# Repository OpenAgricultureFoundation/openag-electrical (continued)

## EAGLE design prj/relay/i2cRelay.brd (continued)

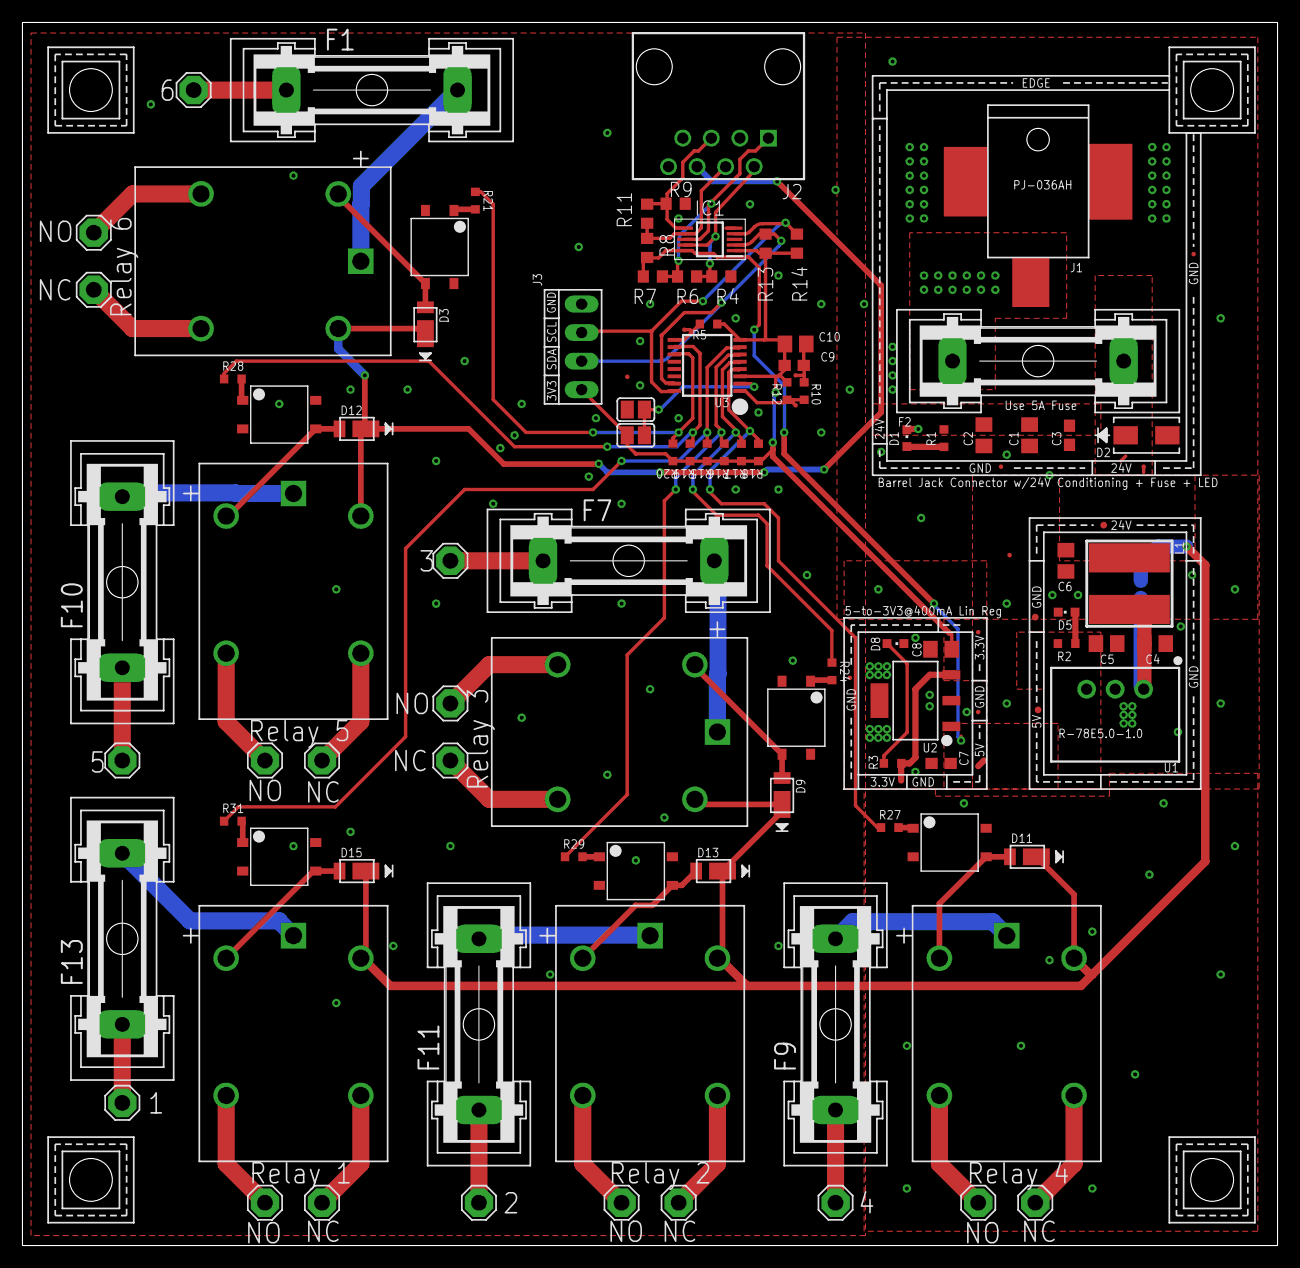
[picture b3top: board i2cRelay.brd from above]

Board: 2 copper layers, 111.7 x 108.9 mm, 120 parts (1 on the bottom side), 60 nets.

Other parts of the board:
U$1, U$2, U$4, U$5: CORNER

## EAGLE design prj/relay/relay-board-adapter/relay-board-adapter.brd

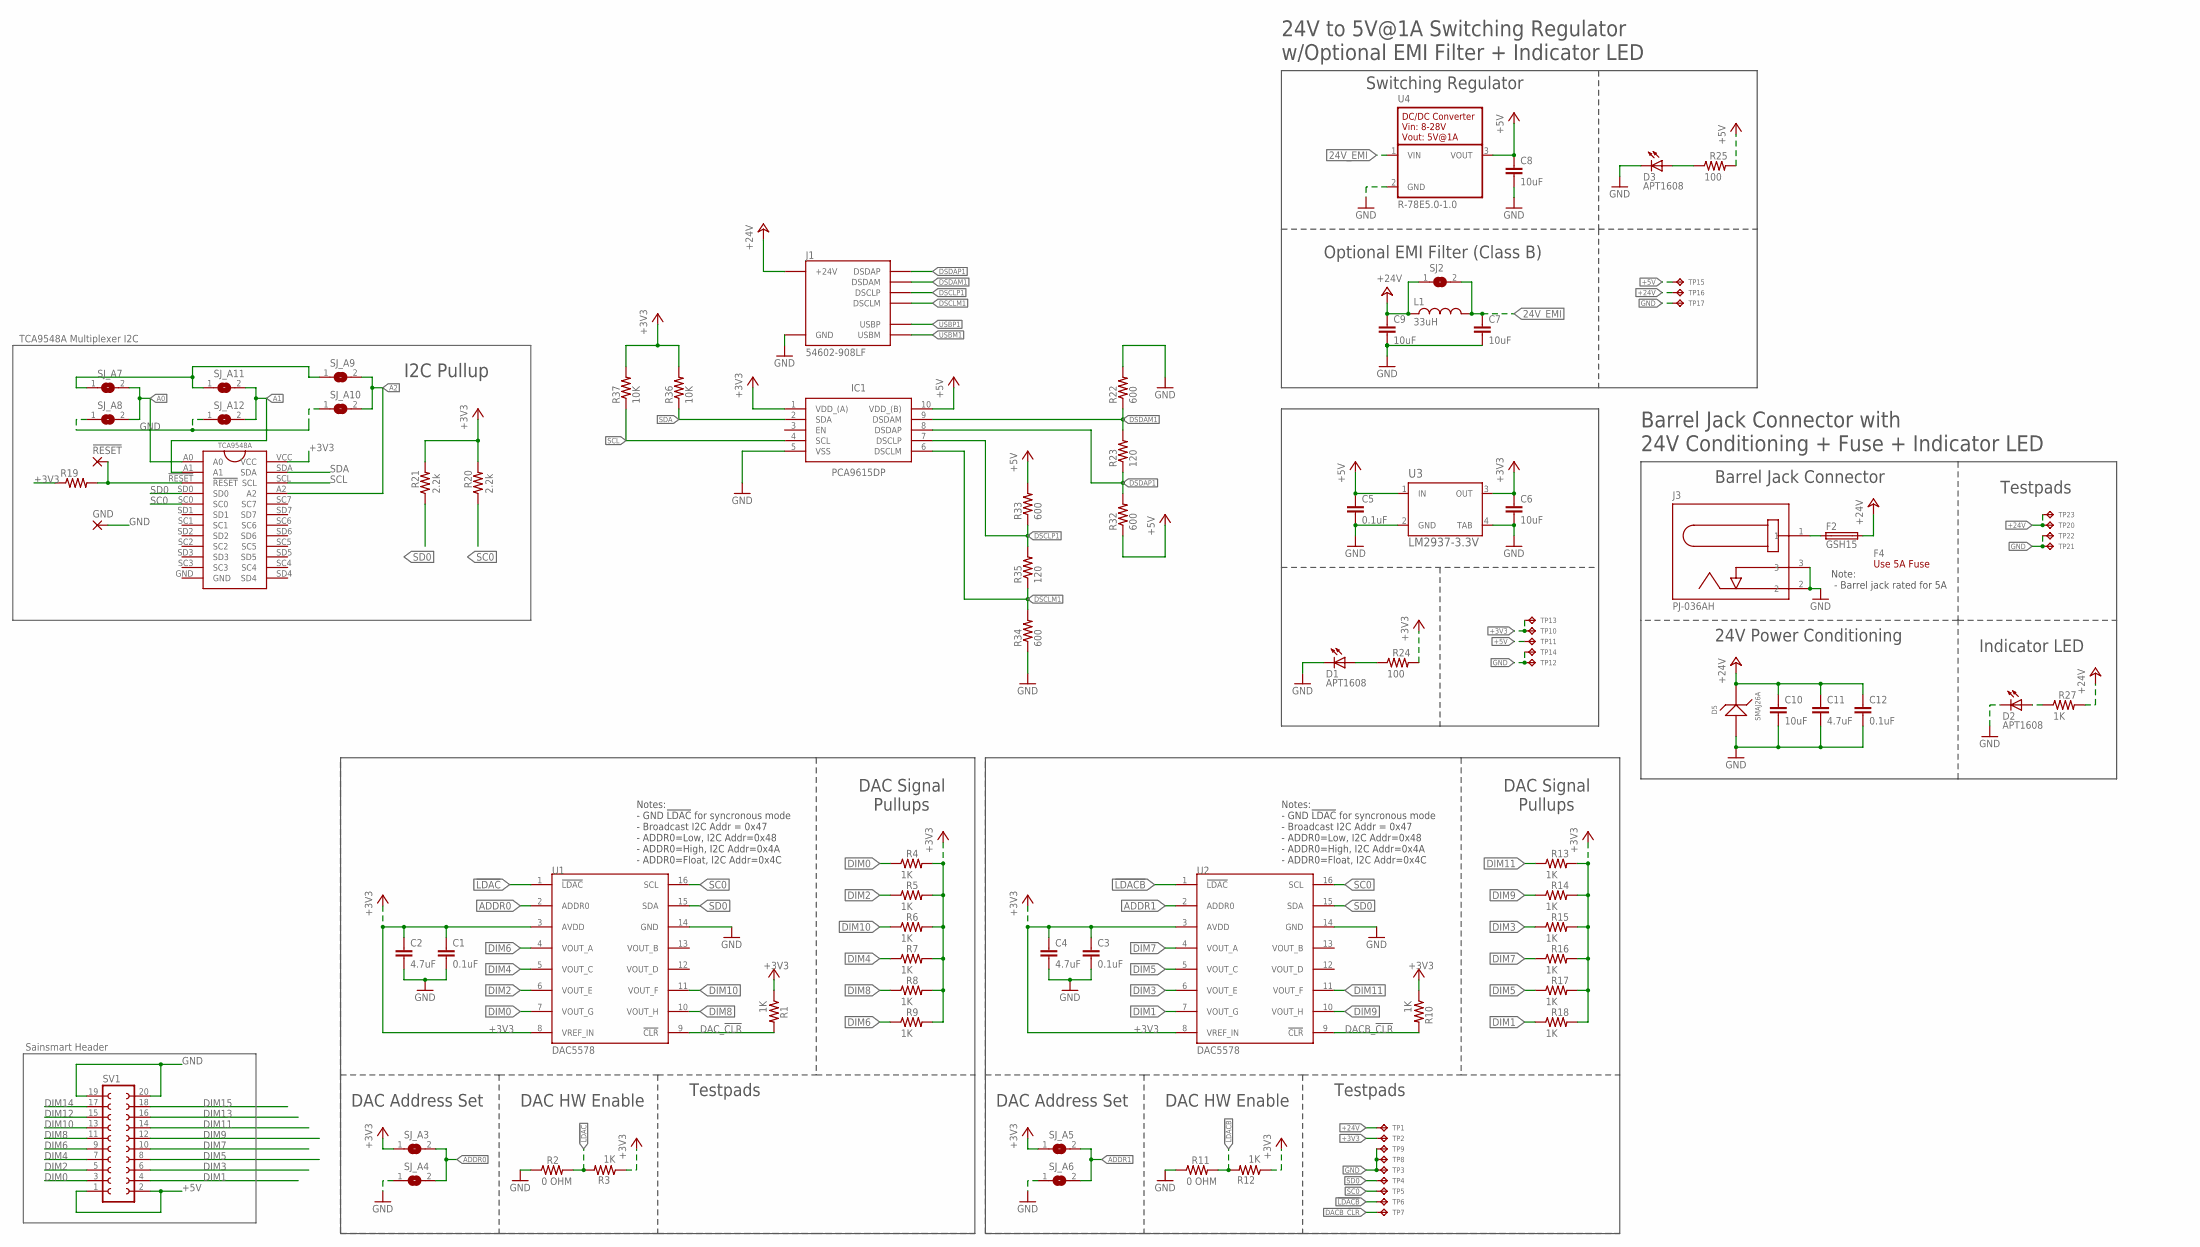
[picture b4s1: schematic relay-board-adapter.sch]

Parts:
!RESET!: 1,6/0,8
C1, C3, C5, C12: 0.1uF; C0603
C2, C4, C11: 4.7uF; C0805
C6, C7, C8, C9, C10: 10uF; C0805
D1, D2, D3: APT1608; CHIPLED_0603
D5: SMAJ26A; SMA
F2: GSH15
F4: Use 5A Fuse; FUSE-CARTRIDGE
GND: 1,6/0,8
IC1: PCA9615DP; SOP50P490X110-10N
J1: 54602-908LF; OPENAG-V1-RJ45
J3: PJ-036AH; BARREL-JACK-PJ-036AH
L1: 33uH; 29333C
R1, R3, R4, R5, R6, R7, R8, R9, R10, R12, R13, R14, R15, R16, R17, R18, R27: 1K; RC0603N
R2, R11: 0 OHM; RC0603N
R19: R-US_R0603; R0603
R20, R21: 2.2k; RC0603N
R22, R32, R33, R34: 600; R0603
R23, R35: 120; R0603
R24, R25: 100; RC0603N
R36, R37: 10K; R0603
SJ2: EMI-BYPASS
SJ_A3, SJ_A4, SJ_A5, SJ_A6, SJ_A7, SJ_A8, SJ_A9, SJ_A10, SJ_A11, SJ_A12: SOLDERJUMPERREFLOW_NOPASTE; SJ1
SV1: FE10-2
TP1, TP2, TP3, TP4, TP5, TP6, TP7, TP8, TP9, TP10, TP11, TP12, TP13, TP14, TP20, TP21, TP22, TP23: TPTP04R; TP04R
TP15, TP16, TP17: TPTP06R; TP06R
U1, U2: DAC5578; TSSOP16
U3: LM2937-3.3V; MP04A
U4: R-78E5.0-1.0
U$1: TCA9548A; TSSOP24

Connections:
24V_EMI: C7.1, L1.2, SJ2.2, U4.1 (VIN)
24V_IN1: F2.1, J3.1
!LDAC!: R2.2, R3.2, U1.1 (!LDAC!)
!LDACB!: R11.2, R12.2, TP6.1, U2.1 (!LDAC!)
!RESET!: !RESET!.1, R19.2, U$1.!RESET!
+3V3: C1.1, C2.1, C3.1, C4.1, C6.1, IC1.1 (VDD_(A)), R1.1, R3.1, R4.2, R5.2, R6.2, R7.2, R8.2, R9.2, R10.1, R12.1, R13.2, R14.2, R15.2, R16.2, R17.2, R18.2, R19.1, R20.2, R21.2, R24.2, R36.2, R37.2, SJ_A3.1, SJ_A5.1, SJ_A7.1, SJ_A9.1, SJ_A11.1, TP2.1, TP10.1, TP13.1, U1.3 (AVDD), U1.8 (VREF_IN), U2.3 (AVDD), U2.8 (VREF_IN), U3.3 (OUT), U$1.VCC
+5V: C5.1, C8.1, IC1.10 (VDD_(B)), R25.2, R32.1, R33.2, SV1.1, SV1.2, TP11.1, TP15.TP, U3.1 (IN), U4.3 (VOUT)
+24V: C9.1, C10.1, C11.1, C12.1, D5.1, F2.2, J1.24V(6) (+24V), L1.1, R27.2, SJ2.1, TP1.1, TP16.TP, TP20.1, TP23.1
A0: SJ_A7.2, SJ_A8.2, U$1.A0
A1: SJ_A11.2, SJ_A12.2, U$1.A1
A2: SJ_A9.2, SJ_A10.2, U$1.A2
ADDR0: SJ_A3.2, SJ_A4.2, U1.2 (ADDR0)
ADDR1: SJ_A5.2, SJ_A6.2, U2.2 (ADDR0)
DACB_!CLR!: R10.2, TP7.1, U2.9 (!CLR!)
DAC_!CLR!: R1.2, U1.9 (!CLR!)
DIM0: R4.1, SV1.3, U1.7 (VOUT_G)
DIM1: R18.1, SV1.4, U2.7 (VOUT_G)
DIM2: R5.1, SV1.5, U1.6 (VOUT_E)
DIM3: R15.1, SV1.6, U2.6 (VOUT_E)
DIM4: R7.1, SV1.7, U1.5 (VOUT_C)
DIM5: R17.1, SV1.8, U2.5 (VOUT_C)
DIM6: R9.1, SV1.9, U1.4 (VOUT_A)
DIM7: R16.1, SV1.10, U2.4 (VOUT_A)
DIM8: R8.1, SV1.11, U1.10 (VOUT_H)
DIM9: R14.1, SV1.12, U2.10 (VOUT_H)
DIM10: R6.1, SV1.13, U1.11 (VOUT_F)
DIM11: R13.1, SV1.14, U2.11 (VOUT_F)
DIM12: SV1.15
DIM13: SV1.16
DIM14: SV1.17
DIM15: SV1.18
DSCLM1: IC1.6 (DSCLM), J1.DSCLM(5) (DSCLM), R34.2, R35.1
DSCLP1: IC1.7 (DSCLP), J1.DSCLP(4) (DSCLP), R33.1, R35.2
DSDAM1: IC1.9 (DSDAM), J1.DSDAM(2) (DSDAM), R22.1, R23.2
DSDAP1: IC1.8 (DSDAP), J1.DSDAP(1) (DSDAP), R23.1, R32.2
GND: C1.2, C2.2, C3.2, C4.2, C5.2, C6.2, C7.2, C8.2, C9.2, C10.2, C11.2, C12.2, D1.C, D2.C, D3.C, D5.2, GND.1, IC1.5 (VSS), J1.GND(3) (GND), J3.2, J3.3, R2.1, R11.1, R22.2, R34.1, SJ_A4.1, SJ_A6.1, SJ_A8.1, SJ_A10.1, SJ_A12.1, SV1.19, SV1.20, TP3.1, TP8.1, TP9.1, TP12.1, TP14.1, TP17.TP, TP21.1, TP22.1, U1.14 (GND), U2.14 (GND), U3.2 (GND), U3.4 (TAB), U4.2 (GND), U$1.GND
unnamed: D1.A, R24.1
unnamed: D2.A, R27.1
unnamed: D3.A, R25.1
SC0: R20.1, TP5.1, U1.16 (SCL), U2.16 (SCL), U$1.SC0
SCL: IC1.4 (SCL), R37.1, U$1.SCL
SD0: R21.1, TP4.1, U1.15 (SDA), U2.15 (SDA), U$1.SD0
SDA: IC1.2 (SDA), R36.1, U$1.SDA
USBM1: J1.USBM(8) (USBM)
USBP1: J1.USBP(7) (USBP)

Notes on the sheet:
Sainsmart Header
Notes: - GND !LDAC! for syncronous mode - Broadcast I2C Addr = 0x47 - ADDR0=Low, I2C Addr=0x48 - ADDR0=High, I2C Addr=0x4A - ADDR0=Float, I2C Addr=0x4C
Testpads
DAC Signal Pullups
DAC Address Set
DAC HW Enable
I2C Pullup
TCA9548A Multiplexer I2C
24V to 5V@1A Switching Regulator w/Optional EMI Filter + Indicator LED
Switching Regulator
Optional EMI Filter (Class B)
Barrel Jack Connector
Barrel Jack Connector with 24V Conditioning + Fuse + Indicator LED
24V Power Conditioning
Indicator LED
Note: - Barrel jack rated for 5A

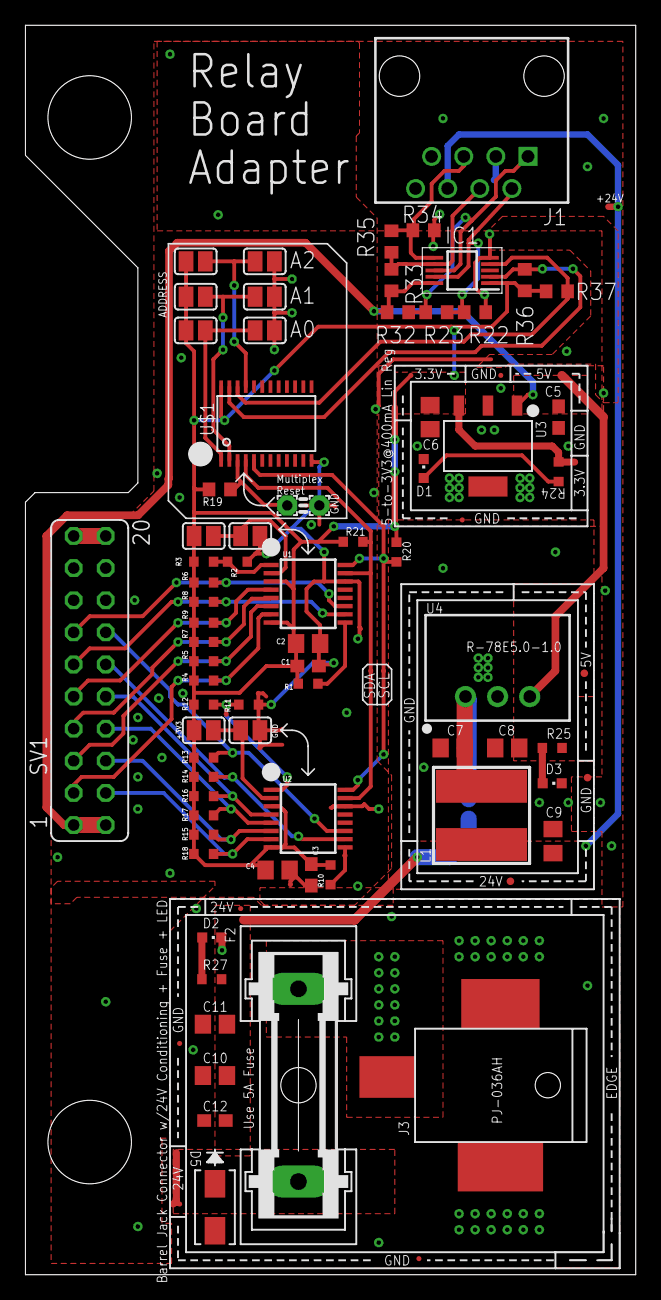
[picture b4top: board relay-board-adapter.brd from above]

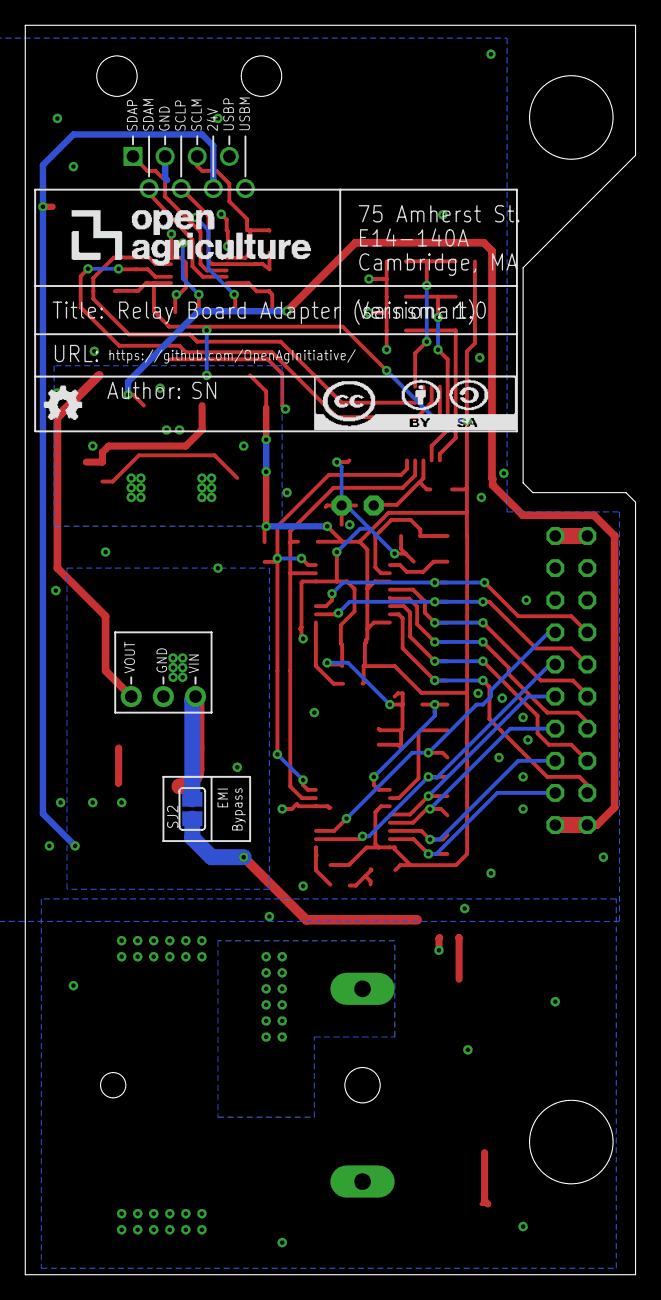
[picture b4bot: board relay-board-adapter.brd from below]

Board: 2 copper layers, 48.3 x 98.8 mm, 95 parts (2 on the bottom side), 39 nets.

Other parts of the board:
ATTRIBUTES: DOCFIELD

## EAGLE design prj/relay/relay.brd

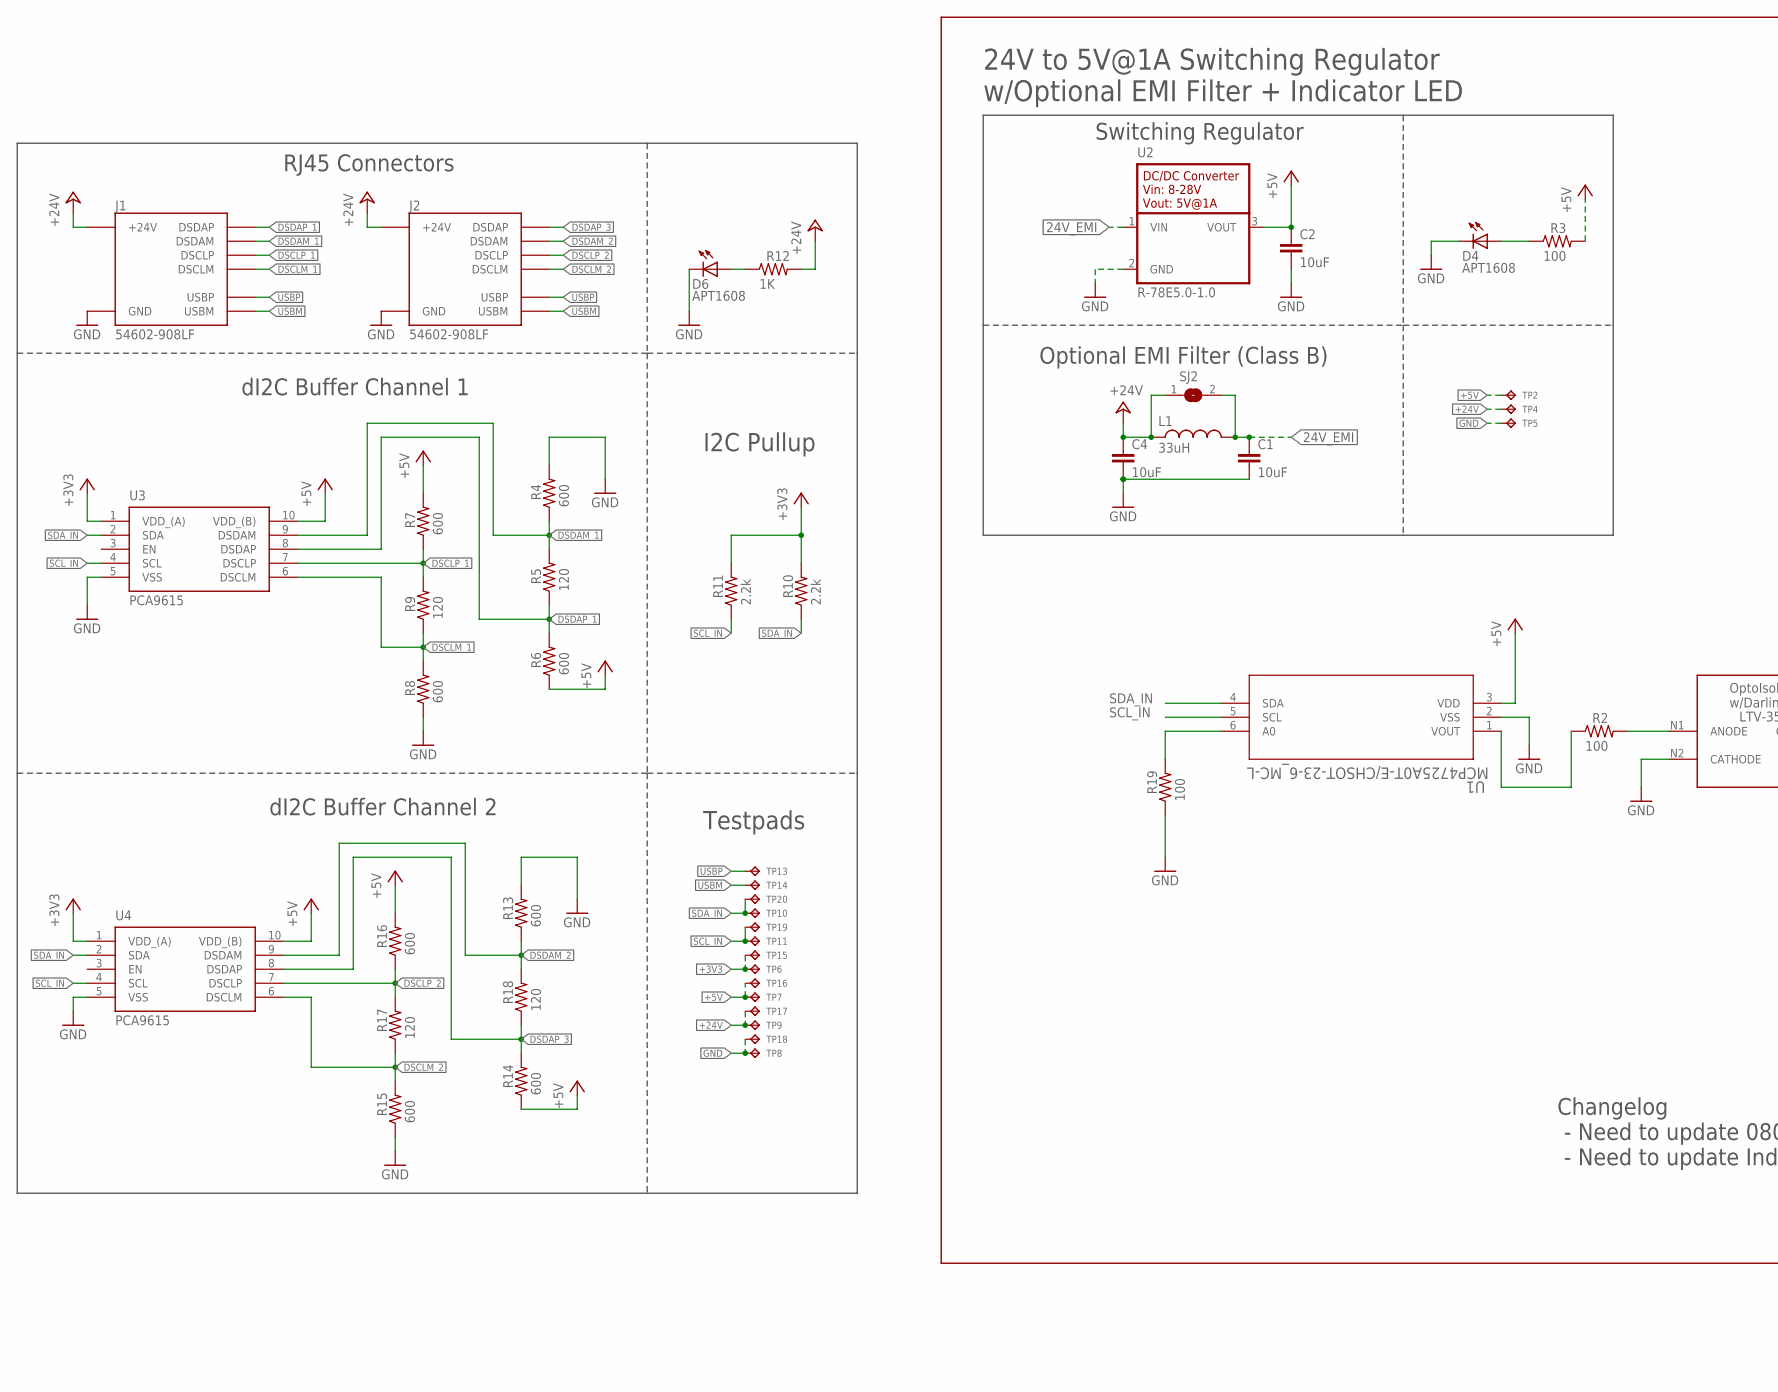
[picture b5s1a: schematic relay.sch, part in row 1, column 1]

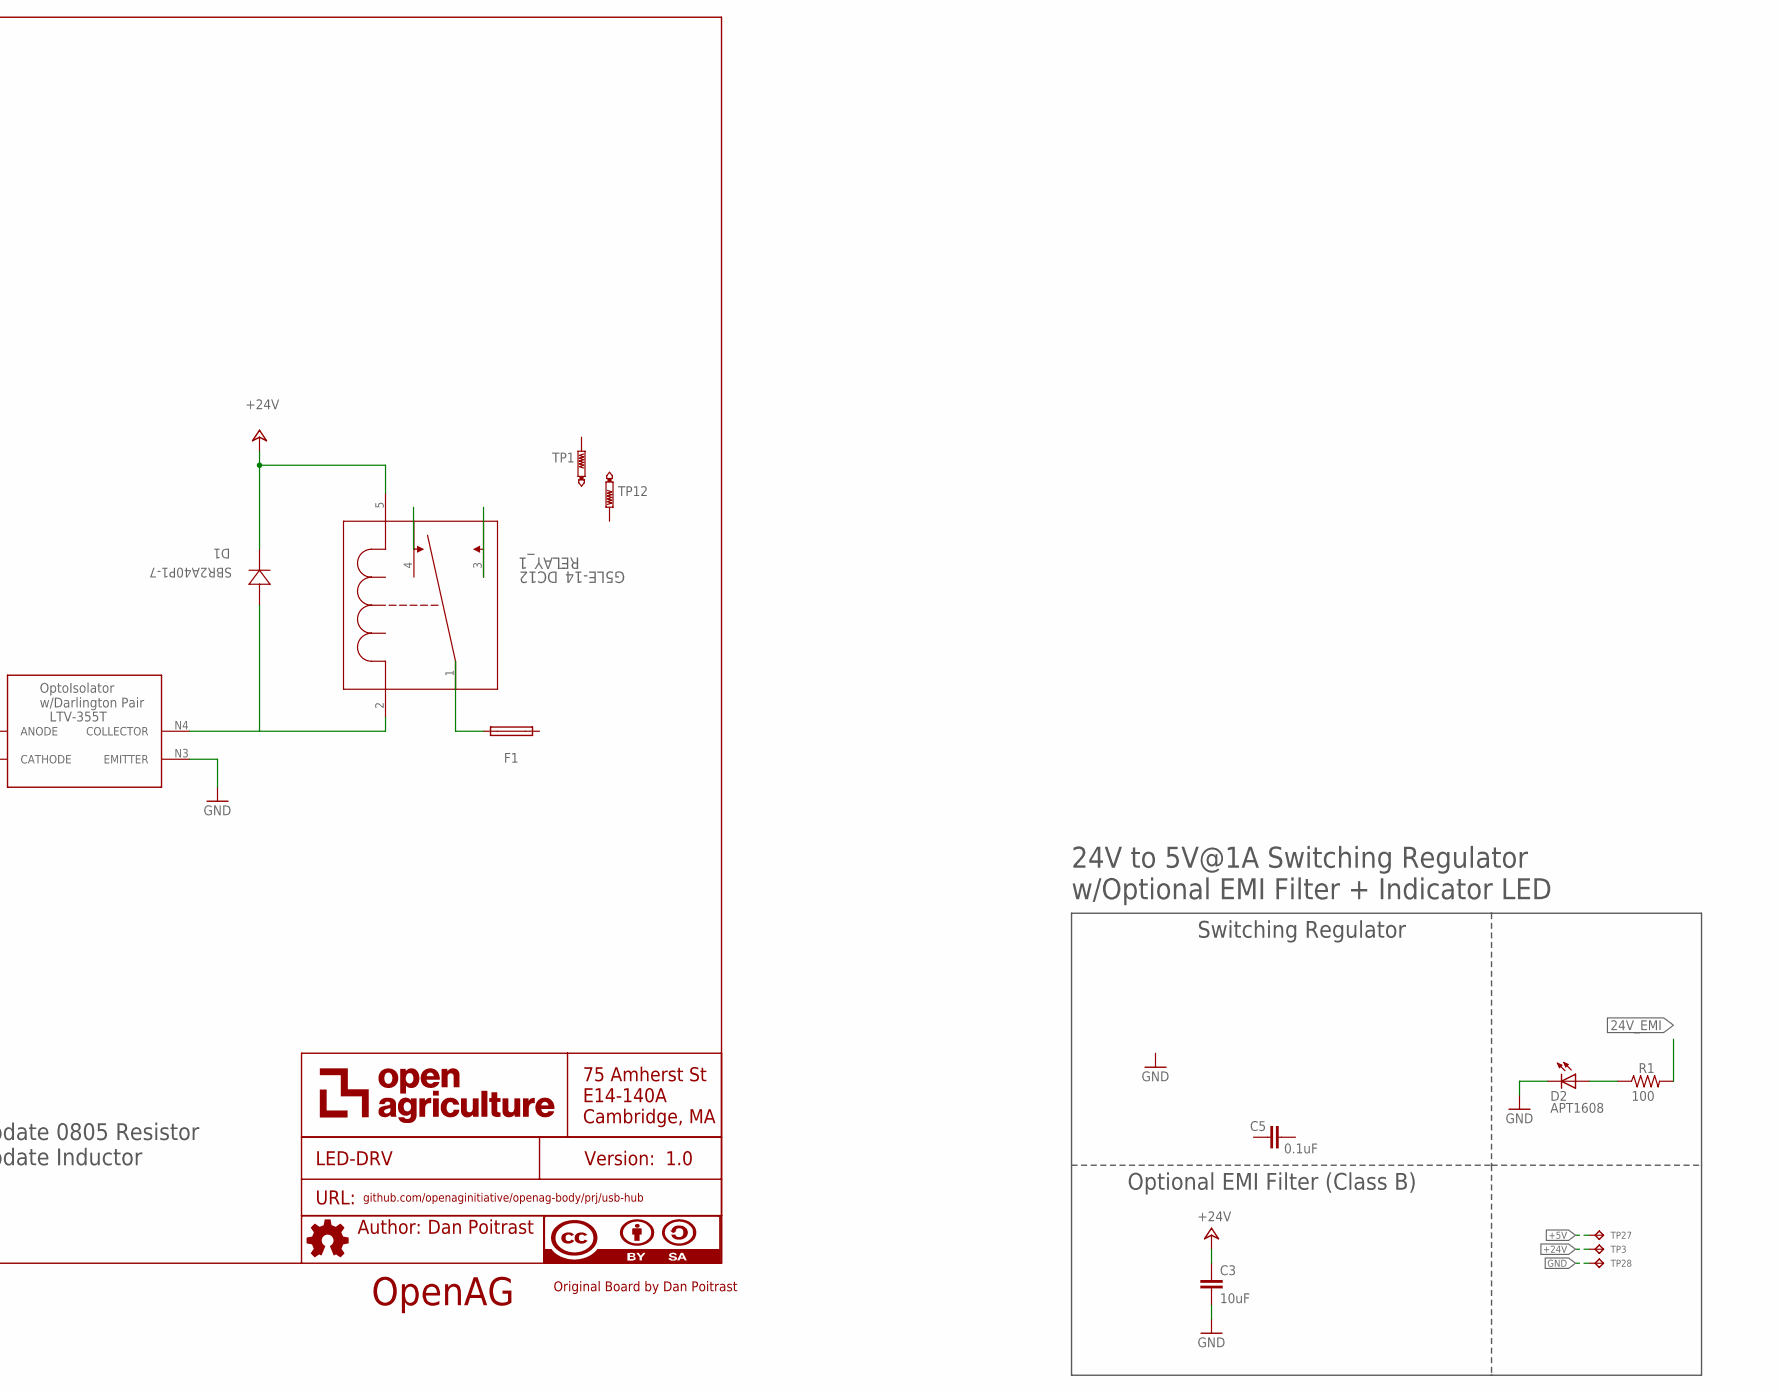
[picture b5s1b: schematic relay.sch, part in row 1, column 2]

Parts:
C1, C2, C3, C4: 10uF; C0805
C5: 0.1uF; C0603
D1: SBR2A40P1-7; POWERDI123
D2, D4, D6: APT1608; CHIPLED_0603
F1: GSH15
J1, J2: 54602-908LF; RJ45-DI2C-USB-54602-908LF
L1: 33uH; 29333C
R1, R2, R3, R19: 100; RC0603N
R4, R6, R7, R8, R13, R14, R15, R16: 600; RC0603N
R5, R9, R17, R18: 120; RC0603N
R10, R11: 2.2k; RC0603N
R12: 1K; RC0603N
RELAY_1: G5LE-14_DC12; RELAY_G5LE-1
SJ2: EMI-BYPASS
TP1, TP12: PTR1B2,54; B2,54
TP2, TP3, TP4, TP5, TP27, TP28: TPTP06R; TP06R
TP6, TP7, TP8, TP9, TP10, TP11, TP13, TP14, TP15, TP16, TP17, TP18, TP19, TP20: TPTP04R; TP04R
U1: MCP4725A0T-E/CHSOT-23-6_MC-L; SOT-23-6_MC-L
U2: R-78E5.0-1.0
U3, U4: PCA9615; SOP50P490X110-10N
U$6: AUTHOR
U$7: TITLE
U$9: LTV-355T

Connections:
24V_EMI: C1.1, L1.2, R1.2, SJ2.2, U2.1 (VIN)
+3V3: R10.2, R11.2, TP6.1, TP15.1, U3.1 (VDD_(A)), U4.1 (VDD_(A))
+5V: C2.1, R3.2, R6.1, R7.2, R14.1, R16.2, TP2.TP, TP7.1, TP16.1, TP27.TP, U1.3 (VDD), U2.3 (VOUT), U3.10 (VDD_(B)), U4.10 (VDD_(B))
+24V: C3.1, C4.1, D1.-, J1.24V(6) (+24V), J2.24V(6) (+24V), L1.1, R12.2, RELAY_1.5, SJ2.1, TP3.TP, TP4.TP, TP9.1, TP17.1
DSCLM_1: J1.DSCLM(5) (DSCLM), R8.2, R9.1, U3.6 (DSCLM)
DSCLM_2: J2.DSCLM(5) (DSCLM), R15.2, R17.1, U4.6 (DSCLM)
DSCLP_1: J1.DSCLP(4) (DSCLP), R7.1, R9.2, U3.7 (DSCLP)
DSCLP_2: J2.DSCLP(4) (DSCLP), R16.1, R17.2, U4.7 (DSCLP)
DSDAM_1: J1.DSDAM(2) (DSDAM), R4.1, R5.2, U3.9 (DSDAM)
DSDAM_2: J2.DSDAM(2) (DSDAM), R13.1, R18.2, U4.9 (DSDAM)
DSDAP_1: J1.DSDAP(1) (DSDAP), R5.1, R6.2, U3.8 (DSDAP)
DSDAP_3: J2.DSDAP(1) (DSDAP), R14.2, R18.1, U4.8 (DSDAP)
GND: C1.2, C2.2, C3.2, C4.2, D2.C, D4.C, D6.C, R4.2, R8.1, R13.2, R15.1, R19.1, TP5.TP, TP8.1, TP18.1, TP28.TP, U1.2 (VSS), U2.2 (GND), U3.5 (VSS), U4.5 (VSS), U$9.N2 (CATHODE), U$9.N3 (EMITTER)
unnamed: D1.+, RELAY_1.2 (1), U$9.N4 (COLLECTOR)
unnamed: D2.A, R1.1
unnamed: F1.2, RELAY_1.1 (2)
unnamed: R2.2, U$9.N1 (ANODE)
unnamed: R2.1, U1.1 (VOUT)
unnamed: R19.2, U1.6 (A0)
unnamed: D4.A, R3.1
unnamed: D6.A, R12.1
SCL_IN: R11.1, TP11.1, TP19.1, U1.5 (SCL), U3.4 (SCL), U4.4 (SCL)
SDA_IN: R10.1, TP10.1, TP20.1, U1.4 (SDA), U3.2 (SDA), U4.2 (SDA)
USBM: J1.USBM(8) (USBM), J2.USBM(8) (USBM), TP14.1
USBP: J1.USBP(7) (USBP), J2.USBP(7) (USBP), TP13.1

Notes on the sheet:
24V to 5V@1A Switching Regulator w/Optional EMI Filter + Indicator LED
Switching Regulator
Optional EMI Filter (Class B)
Changelog - Need to update 0805 Resistor - Need to update Inductor
OpenAG
Original Board by Dan Poitrast
LTV-355T
dI2C Buffer Channel 1
RJ45 Connectors
dI2C Buffer Channel 2
Testpads
I2C Pullup

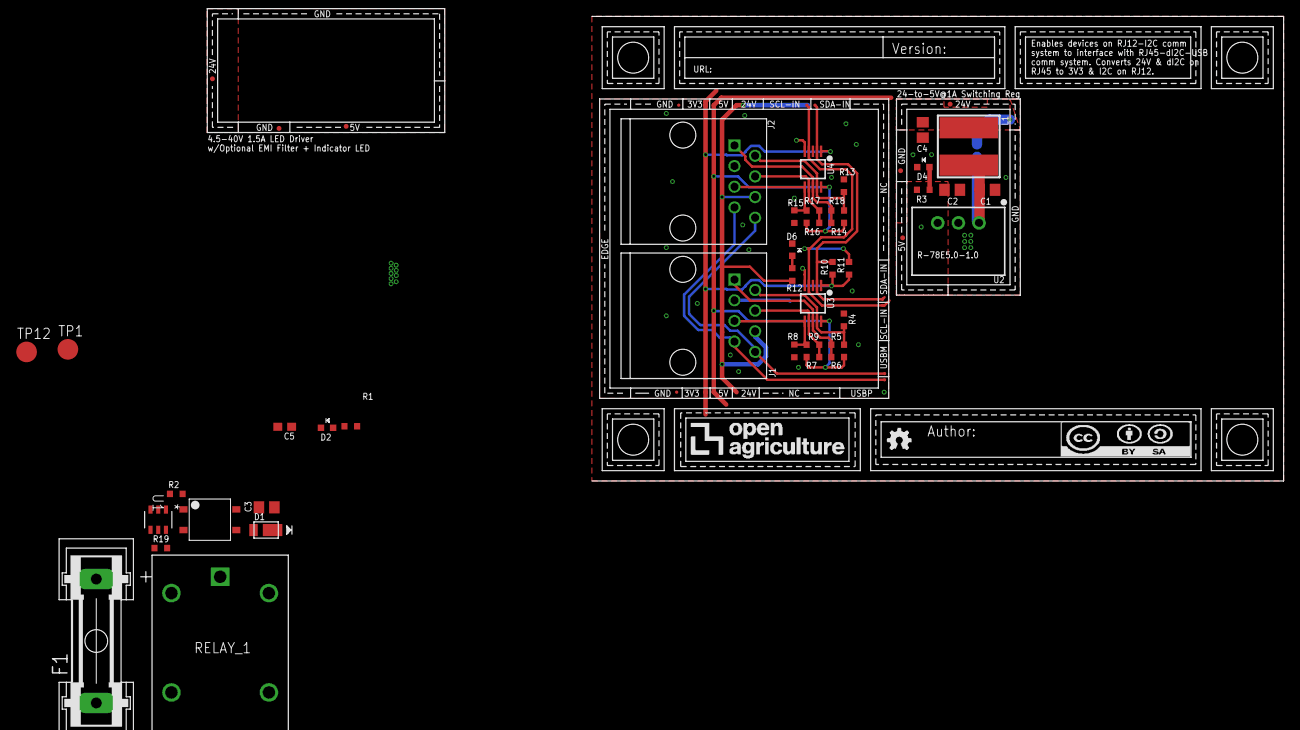
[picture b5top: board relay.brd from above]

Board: 2 copper layers, 68 parts (1 on the bottom side), 25 nets.

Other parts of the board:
U$1, U$2, U$3, U$4: CORNER
U$5: LOGO

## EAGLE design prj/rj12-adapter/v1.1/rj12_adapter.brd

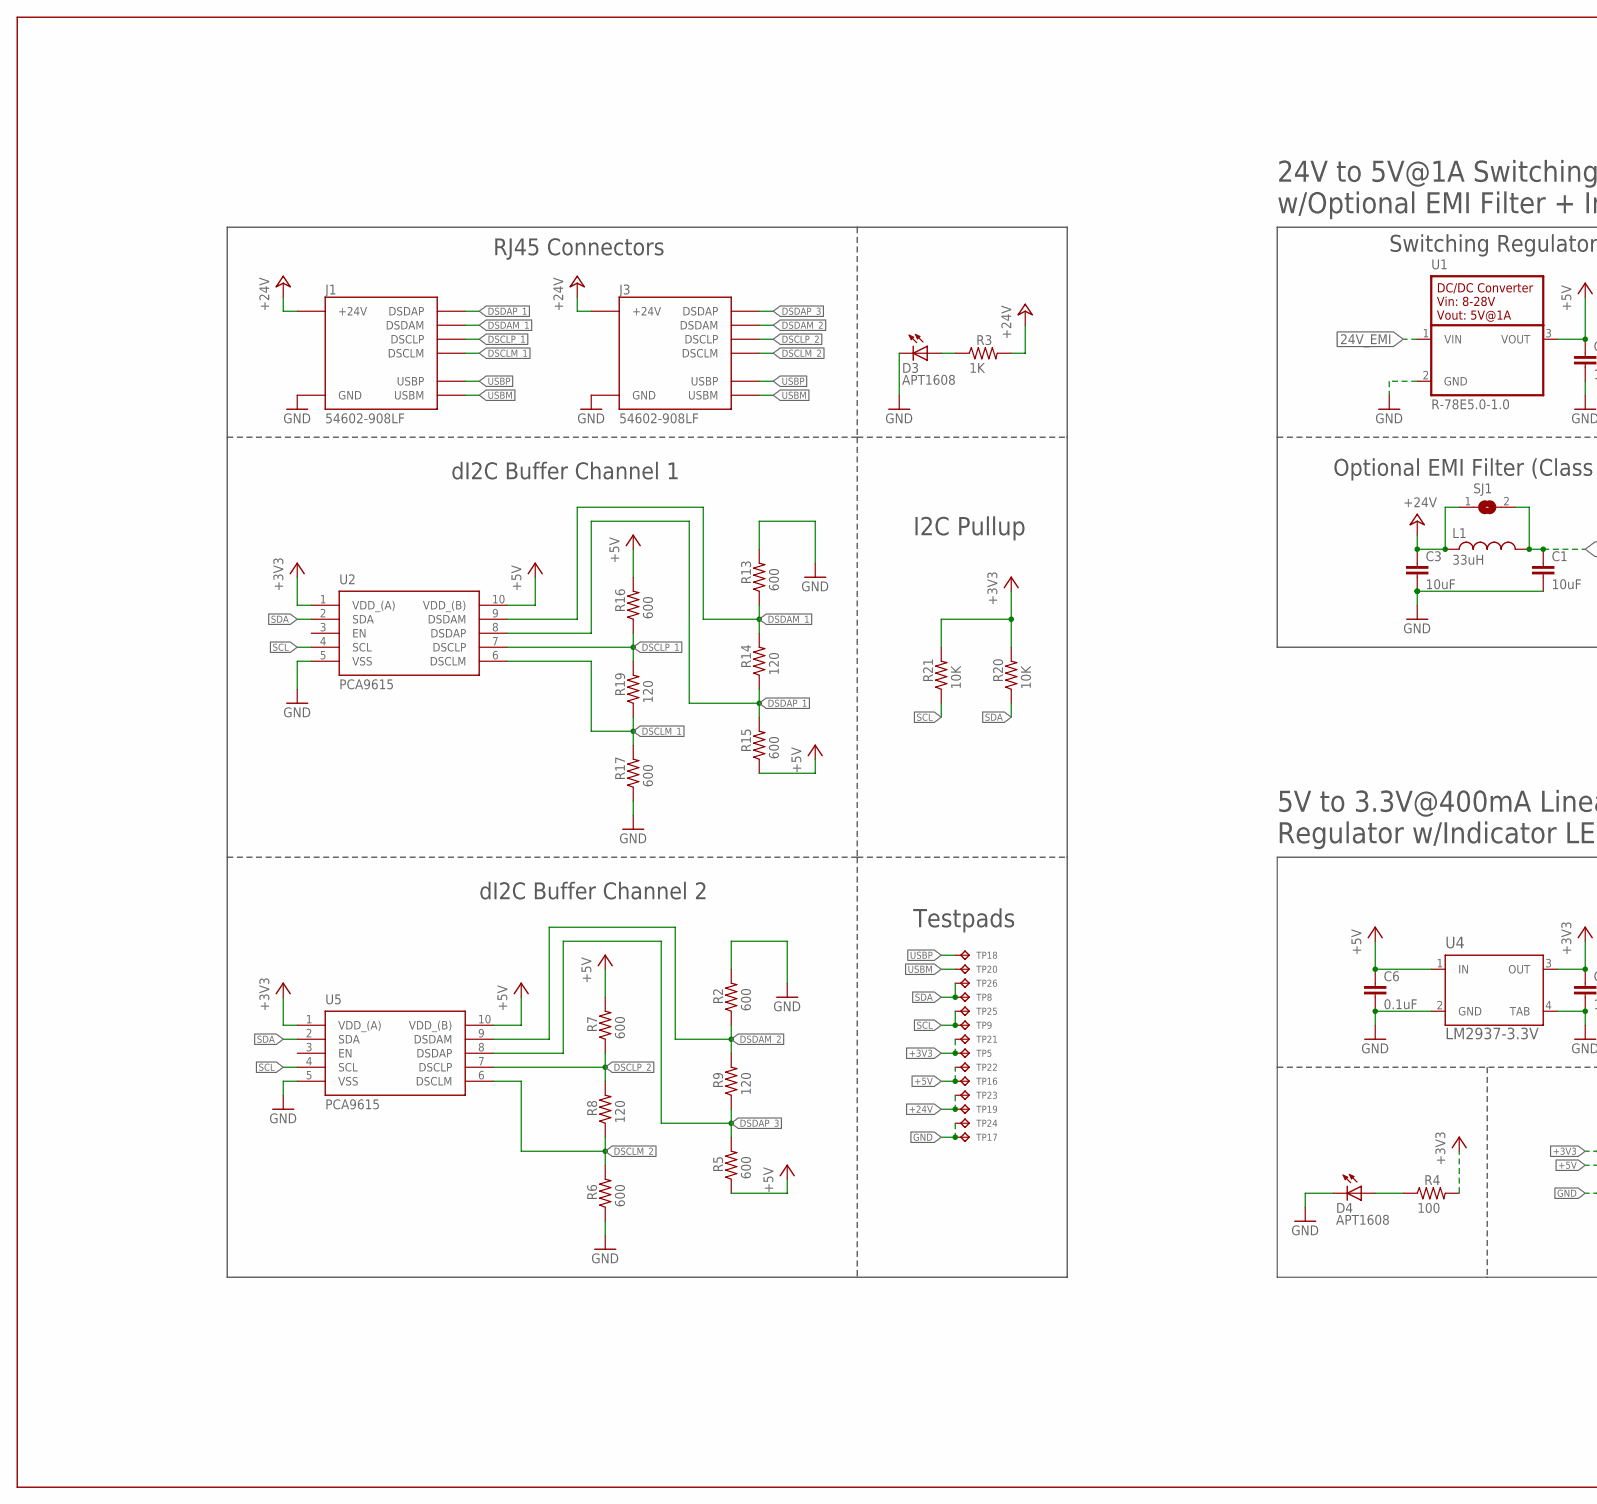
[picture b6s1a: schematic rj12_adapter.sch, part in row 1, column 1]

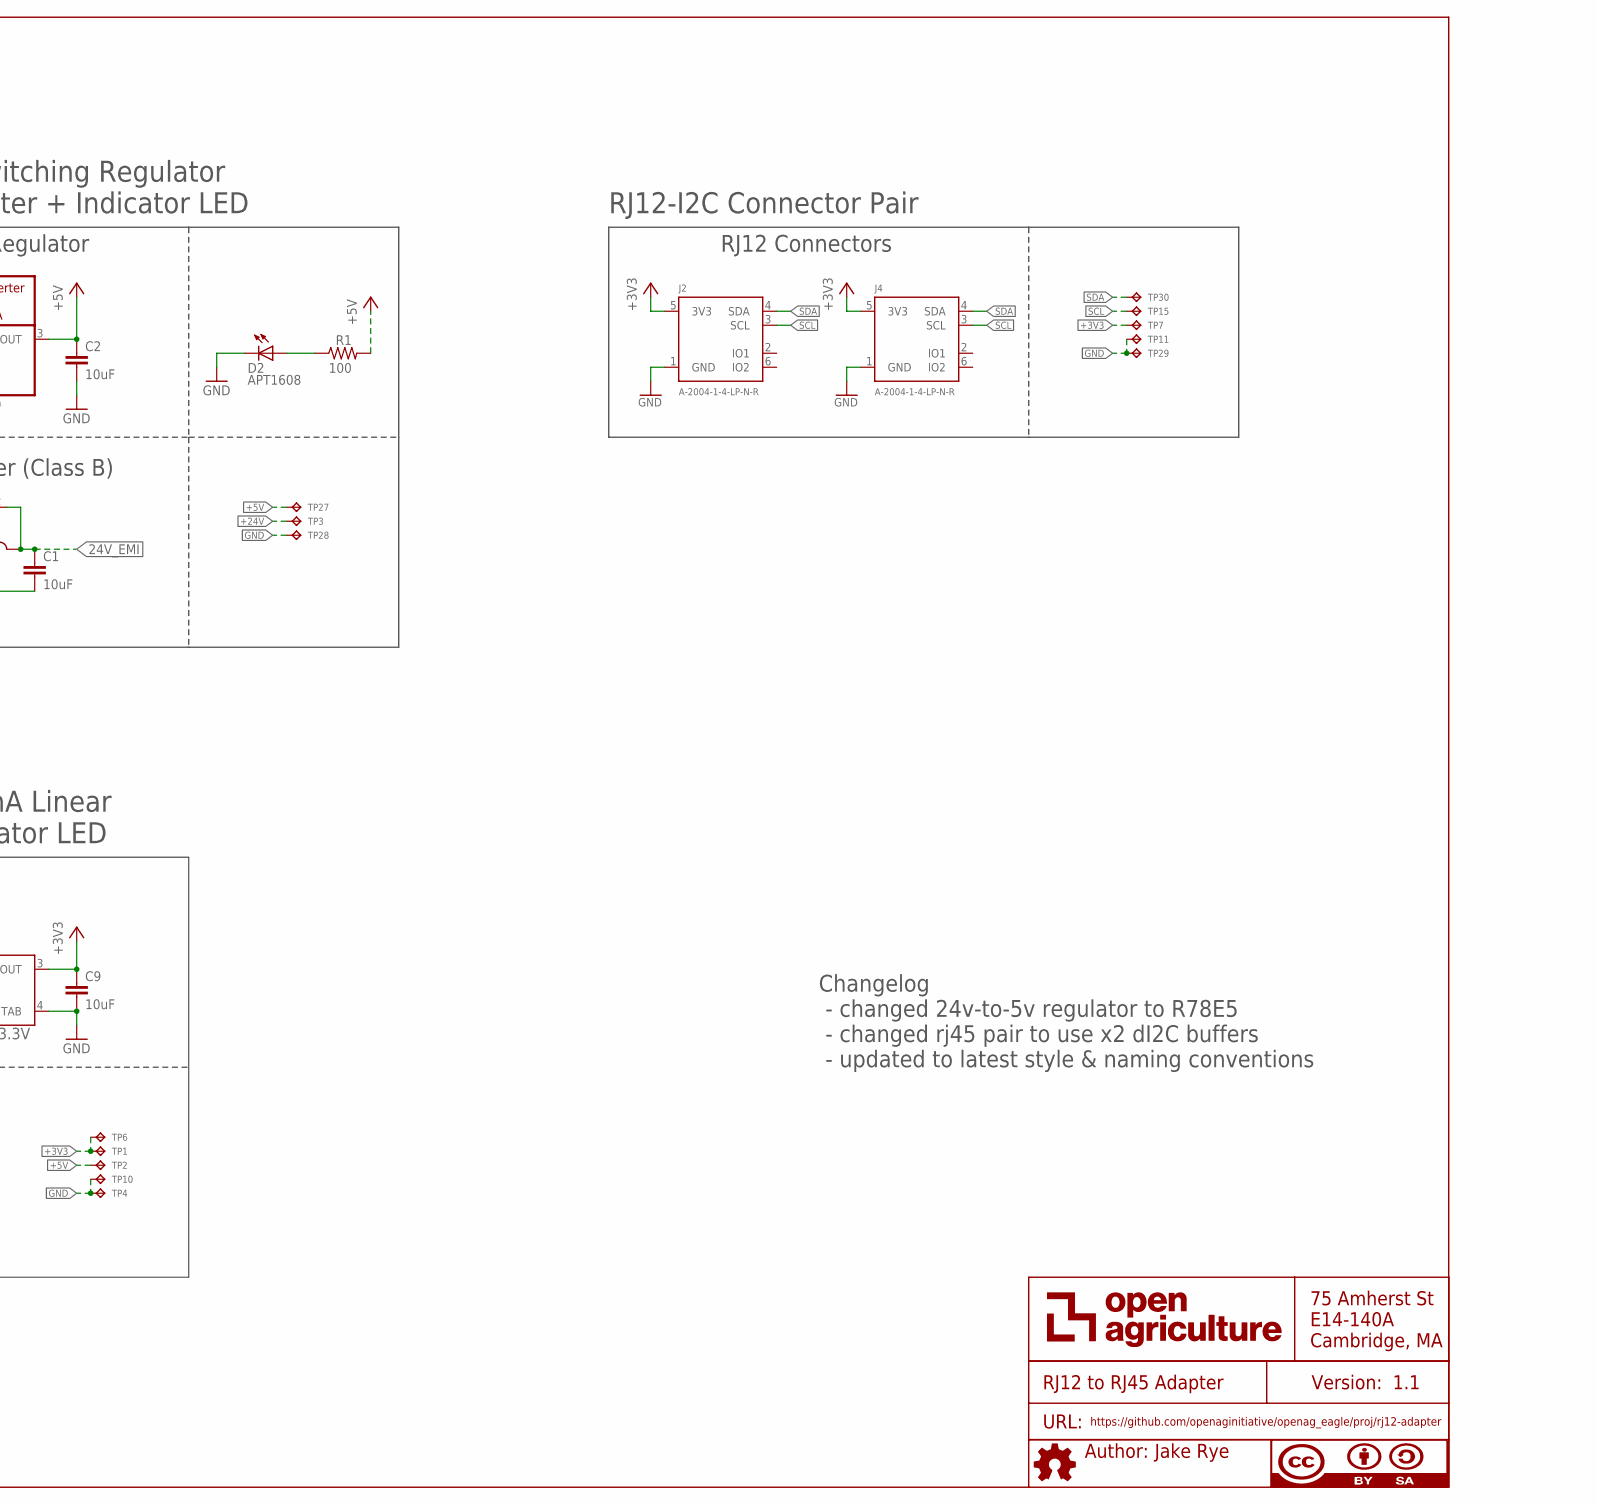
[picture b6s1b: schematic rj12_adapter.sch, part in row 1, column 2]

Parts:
C1, C2, C3, C9: 10uF; C0805
C6: 0.1uF; C0603
D2, D3, D4: APT1608; CHIPLED_0603
J1, J3: 54602-908LF; RJ45-DI2C-USB-54602-908LF
J2, J4: A-2004-1-4-LP-N-R; RJ12-I2C-A-2004-1-4-LP-N-R
L1: 33uH; 29333C
R1, R4: 100; RC0603N
R2, R5, R6, R7, R13, R15, R16, R17: 600; RC0603N
R3: 1K; RC0603N
R8, R9, R14, R19: 120; RC0603N
R20, R21: 10K; RC0603N
SJ1: SOLDERJUMPERREFLOW_NOPASTE; SJ1
TP1, TP2, TP4, TP5, TP6, TP7, TP8, TP9, TP10, TP11, TP15, TP16, TP17, TP18, TP19, TP20, TP21, TP22, TP23, TP24, TP25, TP26, TP29, TP30: TPTP04R; TP04R
TP3, TP27, TP28: TPTP06R; TP06R
U1: R-78E5.0-1.0
U2, U5: PCA9615; SOP50P490X110-10N
U4: LM2937-3.3V; MP04A
U$6: AUTHOR
U$7: TITLE

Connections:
24V_EMI: C1.1, L1.2, SJ1.2, U1.1 (VIN)
+3V3: C9.1, J2.5 (3V3), J4.5 (3V3), R4.2, R20.2, R21.2, TP1.1, TP5.1, TP6.1, TP7.1, TP21.1, U2.1 (VDD_(A)), U4.3 (OUT), U5.1 (VDD_(A))
+5V: C2.1, C6.1, R1.2, R5.1, R7.2, R15.1, R16.2, TP2.1, TP16.1, TP22.1, TP27.TP, U1.3 (VOUT), U2.10 (VDD_(B)), U4.1 (IN), U5.10 (VDD_(B))
+24V: C3.1, J1.24V(6) (+24V), J3.24V(6) (+24V), L1.1, R3.2, SJ1.1, TP3.TP, TP19.1, TP23.1
DSCLM_1: J1.DSCLM(5) (DSCLM), R17.2, R19.1, U2.6 (DSCLM)
DSCLM_2: J3.DSCLM(5) (DSCLM), R6.2, R8.1, U5.6 (DSCLM)
DSCLP_1: J1.DSCLP(4) (DSCLP), R16.1, R19.2, U2.7 (DSCLP)
DSCLP_2: J3.DSCLP(4) (DSCLP), R7.1, R8.2, U5.7 (DSCLP)
DSDAM_1: J1.DSDAM(2) (DSDAM), R13.1, R14.2, U2.9 (DSDAM)
DSDAM_2: J3.DSDAM(2) (DSDAM), R2.1, R9.2, U5.9 (DSDAM)
DSDAP_1: J1.DSDAP(1) (DSDAP), R14.1, R15.2, U2.8 (DSDAP)
DSDAP_3: J3.DSDAP(1) (DSDAP), R5.2, R9.1, U5.8 (DSDAP)
GND: C1.2, C2.2, C3.2, C6.2, C9.2, D2.C, D3.C, D4.C, J1.GND(3) (GND), J2.1 (GND), J3.GND(3) (GND), J4.1 (GND), R2.2, R6.1, R13.2, R17.1, TP4.1, TP10.1, TP11.1, TP17.1, TP24.1, TP28.TP, TP29.1, U1.2 (GND), U2.5 (VSS), U4.2 (GND), U4.4 (TAB), U5.5 (VSS)
unnamed: D4.A, R4.1
unnamed: D2.A, R1.1
unnamed: D3.A, R3.1
SCL: J2.3 (SCL), J4.3 (SCL), R21.1, TP9.1, TP15.1, TP25.1, U2.4 (SCL), U5.4 (SCL)
SDA: J2.4 (SDA), J4.4 (SDA), R20.1, TP8.1, TP26.1, TP30.1, U2.2 (SDA), U5.2 (SDA)
USBM: J1.USBM(8) (USBM), J3.USBM(8) (USBM), TP20.1
USBP: J1.USBP(7) (USBP), J3.USBP(7) (USBP), TP18.1

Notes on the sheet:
5V to 3.3V@400mA Linear Regulator w/Indicator LED
dI2C Buffer Channel 1
RJ45 Connectors
RJ12-I2C Connector Pair
24V to 5V@1A Switching Regulator w/Optional EMI Filter + Indicator LED
Switching Regulator
Optional EMI Filter (Class B)
dI2C Buffer Channel 2
Testpads
I2C Pullup
RJ12 Connectors
Changelog - changed 24v-to-5v regulator to R78E5 - changed rj45 pair to use x2 dI2C buffers - updated to latest style & naming conventions
